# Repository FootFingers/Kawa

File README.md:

# Kawa-HotSwap
## A 32 key 'fixed-split' pro-micro based keyboard with a 128x64 OLED display.

Forked from CoffeeBreakKeyboards [here](https://github.com/CoffeeBreakKeyboards/kawa) and updated to use Kailh Hotswap Sockets. 

A sandwich mount case was also created based on the original Kawa PCB footprint. The central section around the OLED and controller board is covered with a sheet of acrylic, and hardware has been added to provide wireless support. 

*Pic of Kawa build courtesy of Porkus*

## Case
Plate files created:
 - Base Plate x1
 - Top Plate x2
 - Acrylic Centre Guard x1

## Firmware

Firmware files are available [here](https://github.com/sofubi/qmk_firmware/tree/kawa/rev0.1/keyboards/handwired/kawa)

Wireless firmware is still currently in development.

## Usage

Use these files at your own risk. This project is currently in development, and as such is likely to contain issues. 

## ToDo
- [ ] Wireless Firmware
- [ ] Build Guide
- [x] PCB updated to use hotswap sockets
- [x] Sandwich Mount Case + Acrylic Component Cover

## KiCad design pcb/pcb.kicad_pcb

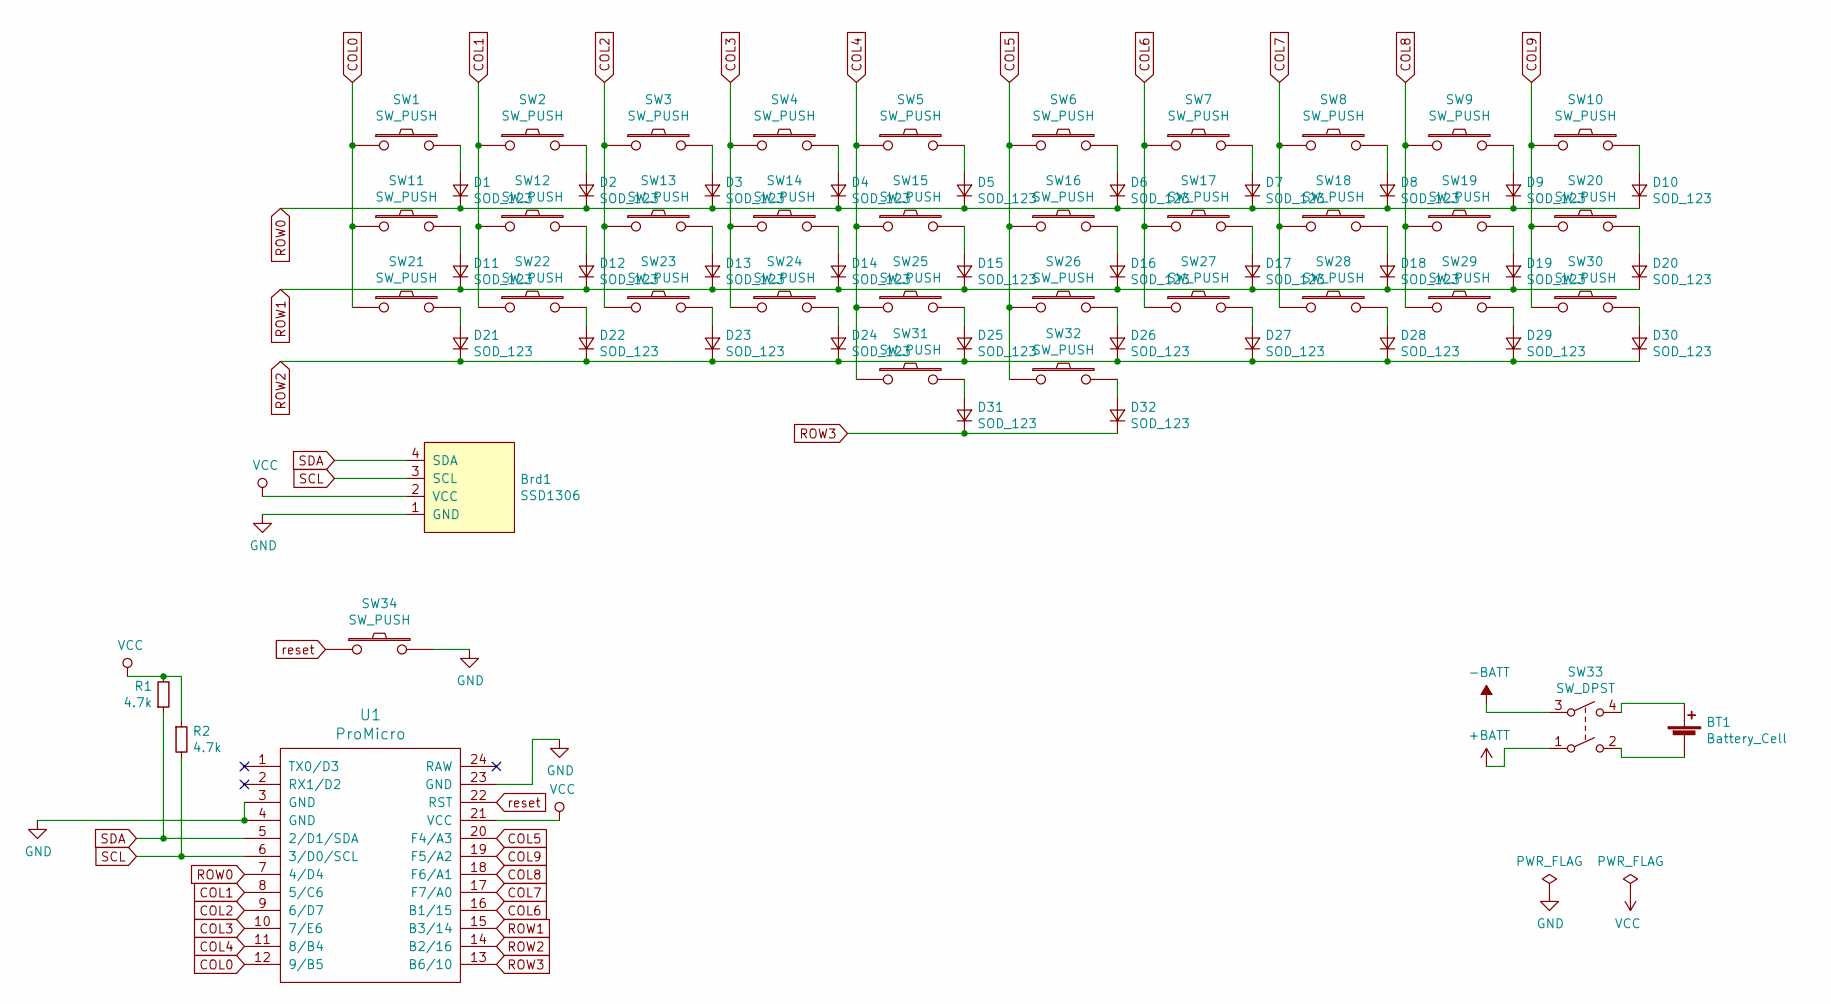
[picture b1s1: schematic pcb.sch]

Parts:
BT1: Battery_Cell; PinHeader_1x02_P2.00mm_Vertical
Brd1: SSD1306; 128x64OLED
D1, D2, D3, D4, D5, D6, D7, D8, D9, D10, D11, D12, D13, D14, D15, D16, D17, D18, D19, D20, D21, D22, D23, D24, D25, D26, D27, D28, D29, D30, D31, D32: SOD_123; D3_TH
R1, R2: 4.7k; R_Axial_DIN0204_L3.6mm_D1.6mm_P1.90mm_Vertical
SW1, SW2, SW3, SW4, SW5, SW6, SW7, SW8, SW9, SW10, SW11, SW12, SW13, SW14, SW15, SW16, SW17, SW18, SW19, SW20, SW21, SW22, SW23, SW24, SW25, SW26, SW27, SW28, SW29, SW30: SW_PUSH; SW_Hotswap_Kailh_1.00u
SW31, SW32: SW_PUSH; MXOnly-2U-Hotswap
SW33: SW_DPST; SW_E-Switch_EG1271_DPDT
SW34: SW_PUSH; ResetSW_1side
U1: ProMicro; ArduinoProMicro

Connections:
+BATT: SW33.1
-BATT: SW33.3
COL0: SW1.1, SW11.1, SW21.1, U1.12 (9/B5)
COL1: SW2.1, SW12.1, SW22.1, U1.8 (5/C6)
COL2: SW3.1, SW13.1, SW23.1, U1.9 (6/D7)
COL3: SW4.1, SW14.1, SW24.1, U1.10 (7/E6)
COL4: SW5.1, SW15.1, SW25.1, SW31.1, U1.11 (8/B4)
COL5: SW6.1, SW16.1, SW26.1, SW32.1, U1.20 (F4/A3)
COL6: SW7.1, SW17.1, SW27.1, U1.16 (B1/15)
COL7: SW8.1, SW18.1, SW28.1, U1.17 (F7/A0)
COL8: SW9.1, SW19.1, SW29.1, U1.18 (F6/A1)
COL9: SW10.1, SW20.1, SW30.1, U1.19 (F5/A2)
GND: Brd1.1 (GND), SW34.2, U1.3 (GND), U1.4 (GND), U1.23 (GND)
unnamed: BT1.1 (+), SW33.4
unnamed: BT1.2 (-), SW33.2
unnamed: D1.2 (A), SW1.2
unnamed: D2.2 (A), SW2.2
unnamed: D3.2 (A), SW3.2
unnamed: D4.2 (A), SW4.2
unnamed: D5.2 (A), SW5.2
unnamed: D6.2 (A), SW6.2
unnamed: D7.2 (A), SW7.2
unnamed: D8.2 (A), SW8.2
unnamed: D9.2 (A), SW9.2
unnamed: D10.2 (A), SW10.2
unnamed: D11.2 (A), SW11.2
unnamed: D12.2 (A), SW12.2
unnamed: D13.2 (A), SW13.2
unnamed: D14.2 (A), SW14.2
unnamed: D15.2 (A), SW15.2
unnamed: D16.2 (A), SW16.2
unnamed: D17.2 (A), SW17.2
unnamed: D18.2 (A), SW18.2
unnamed: D19.2 (A), SW19.2
unnamed: D20.2 (A), SW20.2
unnamed: D21.2 (A), SW21.2
unnamed: D22.2 (A), SW22.2
unnamed: D23.2 (A), SW23.2
unnamed: D24.2 (A), SW24.2
unnamed: D25.2 (A), SW25.2
unnamed: D26.2 (A), SW26.2
unnamed: D27.2 (A), SW27.2
unnamed: D28.2 (A), SW28.2
unnamed: D29.2 (A), SW29.2
unnamed: D30.2 (A), SW30.2
unnamed: D31.2 (A), SW31.2
unnamed: D32.2 (A), SW32.2
ROW0: D1.1 (K), D2.1 (K), D3.1 (K), D4.1 (K), D5.1 (K), D6.1 (K), D7.1 (K), D8.1 (K), D9.1 (K), D10.1 (K), U1.7 (4/D4)
ROW1: D11.1 (K), D12.1 (K), D13.1 (K), D14.1 (K), D15.1 (K), D16.1 (K), D17.1 (K), D18.1 (K), D19.1 (K), D20.1 (K), U1.15 (B3/14)
ROW2: D21.1 (K), D22.1 (K), D23.1 (K), D24.1 (K), D25.1 (K), D26.1 (K), D27.1 (K), D28.1 (K), D29.1 (K), D30.1 (K), U1.14 (B2/16)
ROW3: D31.1 (K), D32.1 (K), U1.13 (B6/10)
SCL: Brd1.3 (SCL), R2.2, U1.6 (3/D0/SCL)
SDA: Brd1.4 (SDA), R1.1, U1.5 (2/D1/SDA)
VCC: Brd1.2 (VCC), R1.2, R2.1, U1.21 (VCC)
reset: SW34.1, U1.22 (RST)

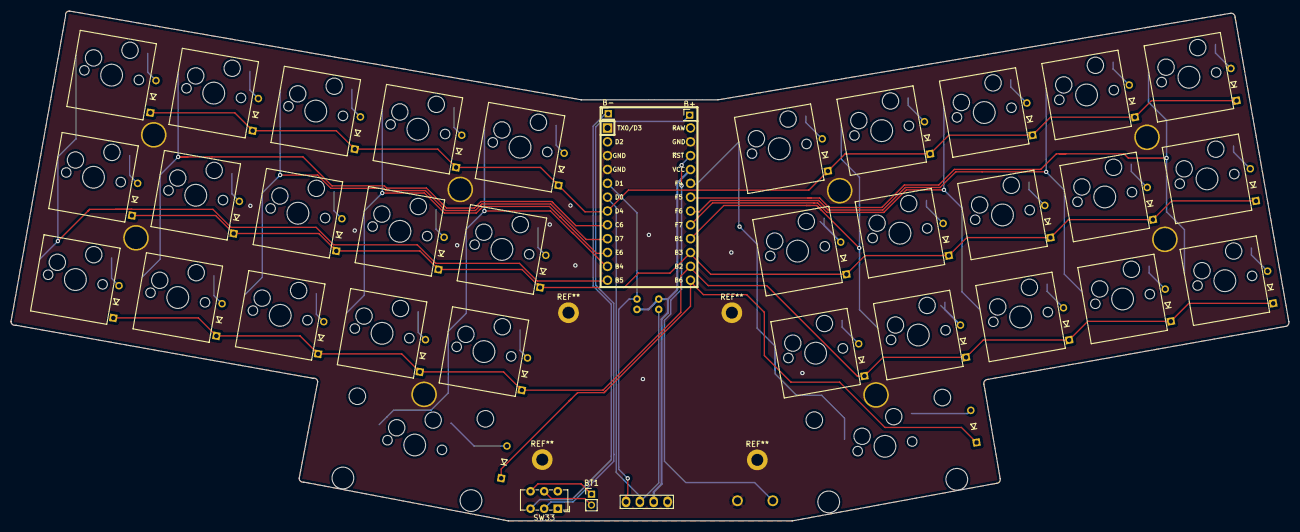
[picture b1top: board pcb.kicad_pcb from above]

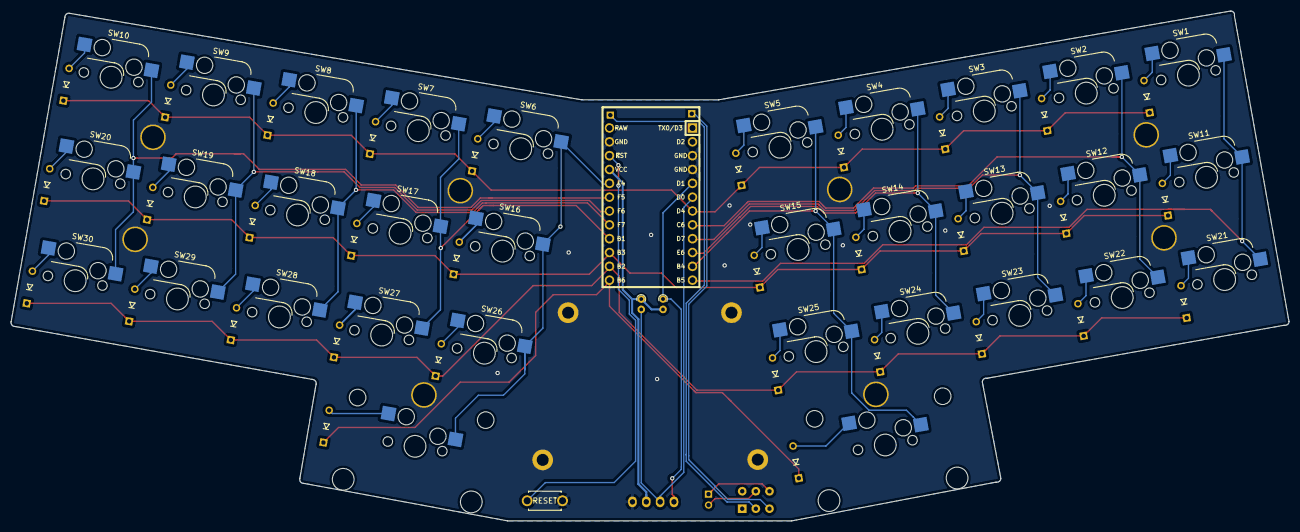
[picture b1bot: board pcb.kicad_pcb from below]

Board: 2 copper layers, 234.6 x 93.6 mm, 81 parts (35 on the bottom side), 53 nets.

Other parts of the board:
B+: PinHeader_1x01_P2.00mm_Vertical
B-: PinHeader_1x01_P2.00mm_Vertical
HOLE_3M, HOLE_3M#2, HOLE_3M#3, HOLE_3M#4, HOLE_3M#5, HOLE_3M#6, HOLE_3M#7, HOLE_3M#8: VAL**; HOLE_M2_TH

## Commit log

2021-12-20 fixed grounded pad + added wireless support
    Grounded pad on 'edc' column fixed.
    Additional pins for nice!nano + on/off switch for battery
2021-12-20 added wireless suport and fixed previous PCB issue
    Added additional header pins for battery usage.
    On/Off switch for battery.
    Support for wireless controller
